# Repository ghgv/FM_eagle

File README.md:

# FM_eagle
Small collpits FM radio

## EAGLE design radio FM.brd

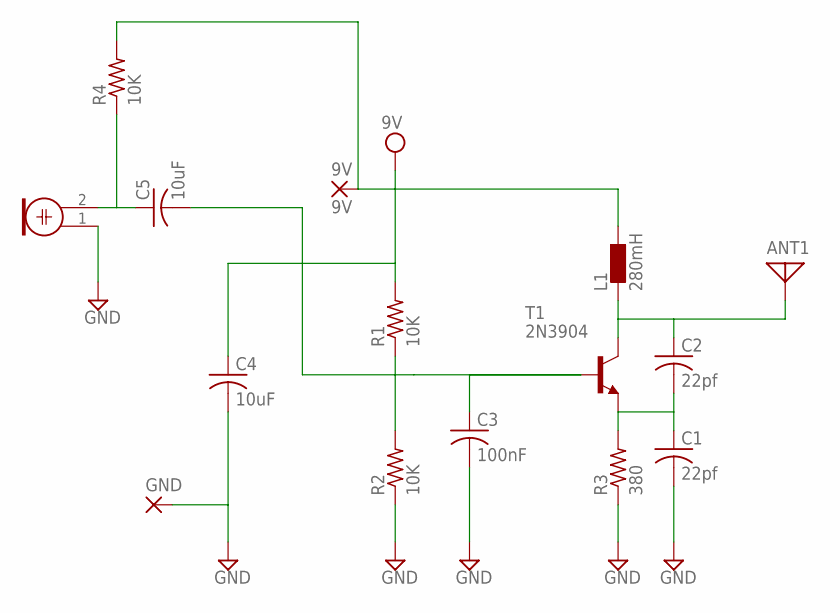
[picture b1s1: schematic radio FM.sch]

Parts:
9V: 9V; 1,6/0,8
ANT1: ANTENNA; PAD-01
C1, C2: 22pf; C050-025X075
C3: 100nF; C050-025X075
C4, C5: 10uF; C050-025X075
GND: 1,6/0,8
L1: 280mH; 0207/10
M1: ELECTRET_MICROPHON-F6035AP; F6035AP
R1, R2, R4: 10K; 0207/7
R3: 380; 0207/7
T1: 2N3904; TO92

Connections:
GND: C1.2, C3.2, C4.2, GND.1, M1.1, R2.1, R3.1
unnamed: C3.1, C5.2, R1.1, R2.2, T1.2 (B)
unnamed: C5.1, M1.2, R4.1
unnamed: C1.1, C2.2, R3.2, T1.3 (E)
unnamed: ANT1.1, C2.1, L1.2, T1.1 (C)
VCC: 9V.1, C4.1, L1.1, R1.2, R4.2

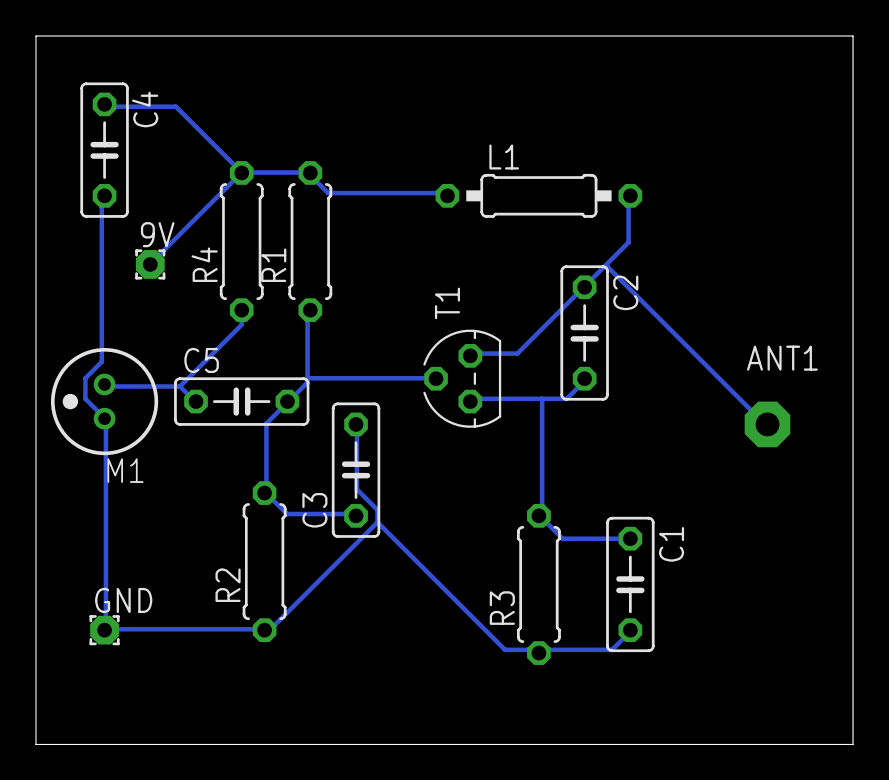
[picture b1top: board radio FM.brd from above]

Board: 2 copper layers, 45.4 x 39.4 mm, 15 parts (0 on the bottom side), 6 nets.

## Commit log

2019-11-14 Version of 2017
